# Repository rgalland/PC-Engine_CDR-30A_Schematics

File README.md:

This repository contains reverse engineering information regarding the PC-Engine CD-ROM2.

It started with the schematics of the main and front PCBs but has now evolve to provide reproduction parts. In the schematics, I attempted to highlight the differences between the CDR-30 (older models) and the CDR-30A but I have even found PCB differences within the newer CDR-30A units. Main difference is the use of the Sony DSP CXD1135 + external RAM as opposed to CXD1167 without additional RAM.
Currently available reproduction parts are the 2 flexible PCBs on the KSS-220A laser module. These are not compatible with the KSS-162A found mainly on older units. The main PCB is at the prototype level at the moment.

You will need kicad to work with files but I also provide pdf files to view the schematics in a more convenent way.

Current versions:
Original PCBs:
	- MAIN_PWR schematics: Rev0.3
	- FRONT_PWB schematics: Rev0.1
	
Reproduction PCBs:
	- KSS-220A Focus Tracking Flex PCB schematics and layout: Rev0.1
	- KSS-220A Lens Flex PCB schematics and layout: Rev0.1
	- Main PCB schematics and layout: Rev0.1

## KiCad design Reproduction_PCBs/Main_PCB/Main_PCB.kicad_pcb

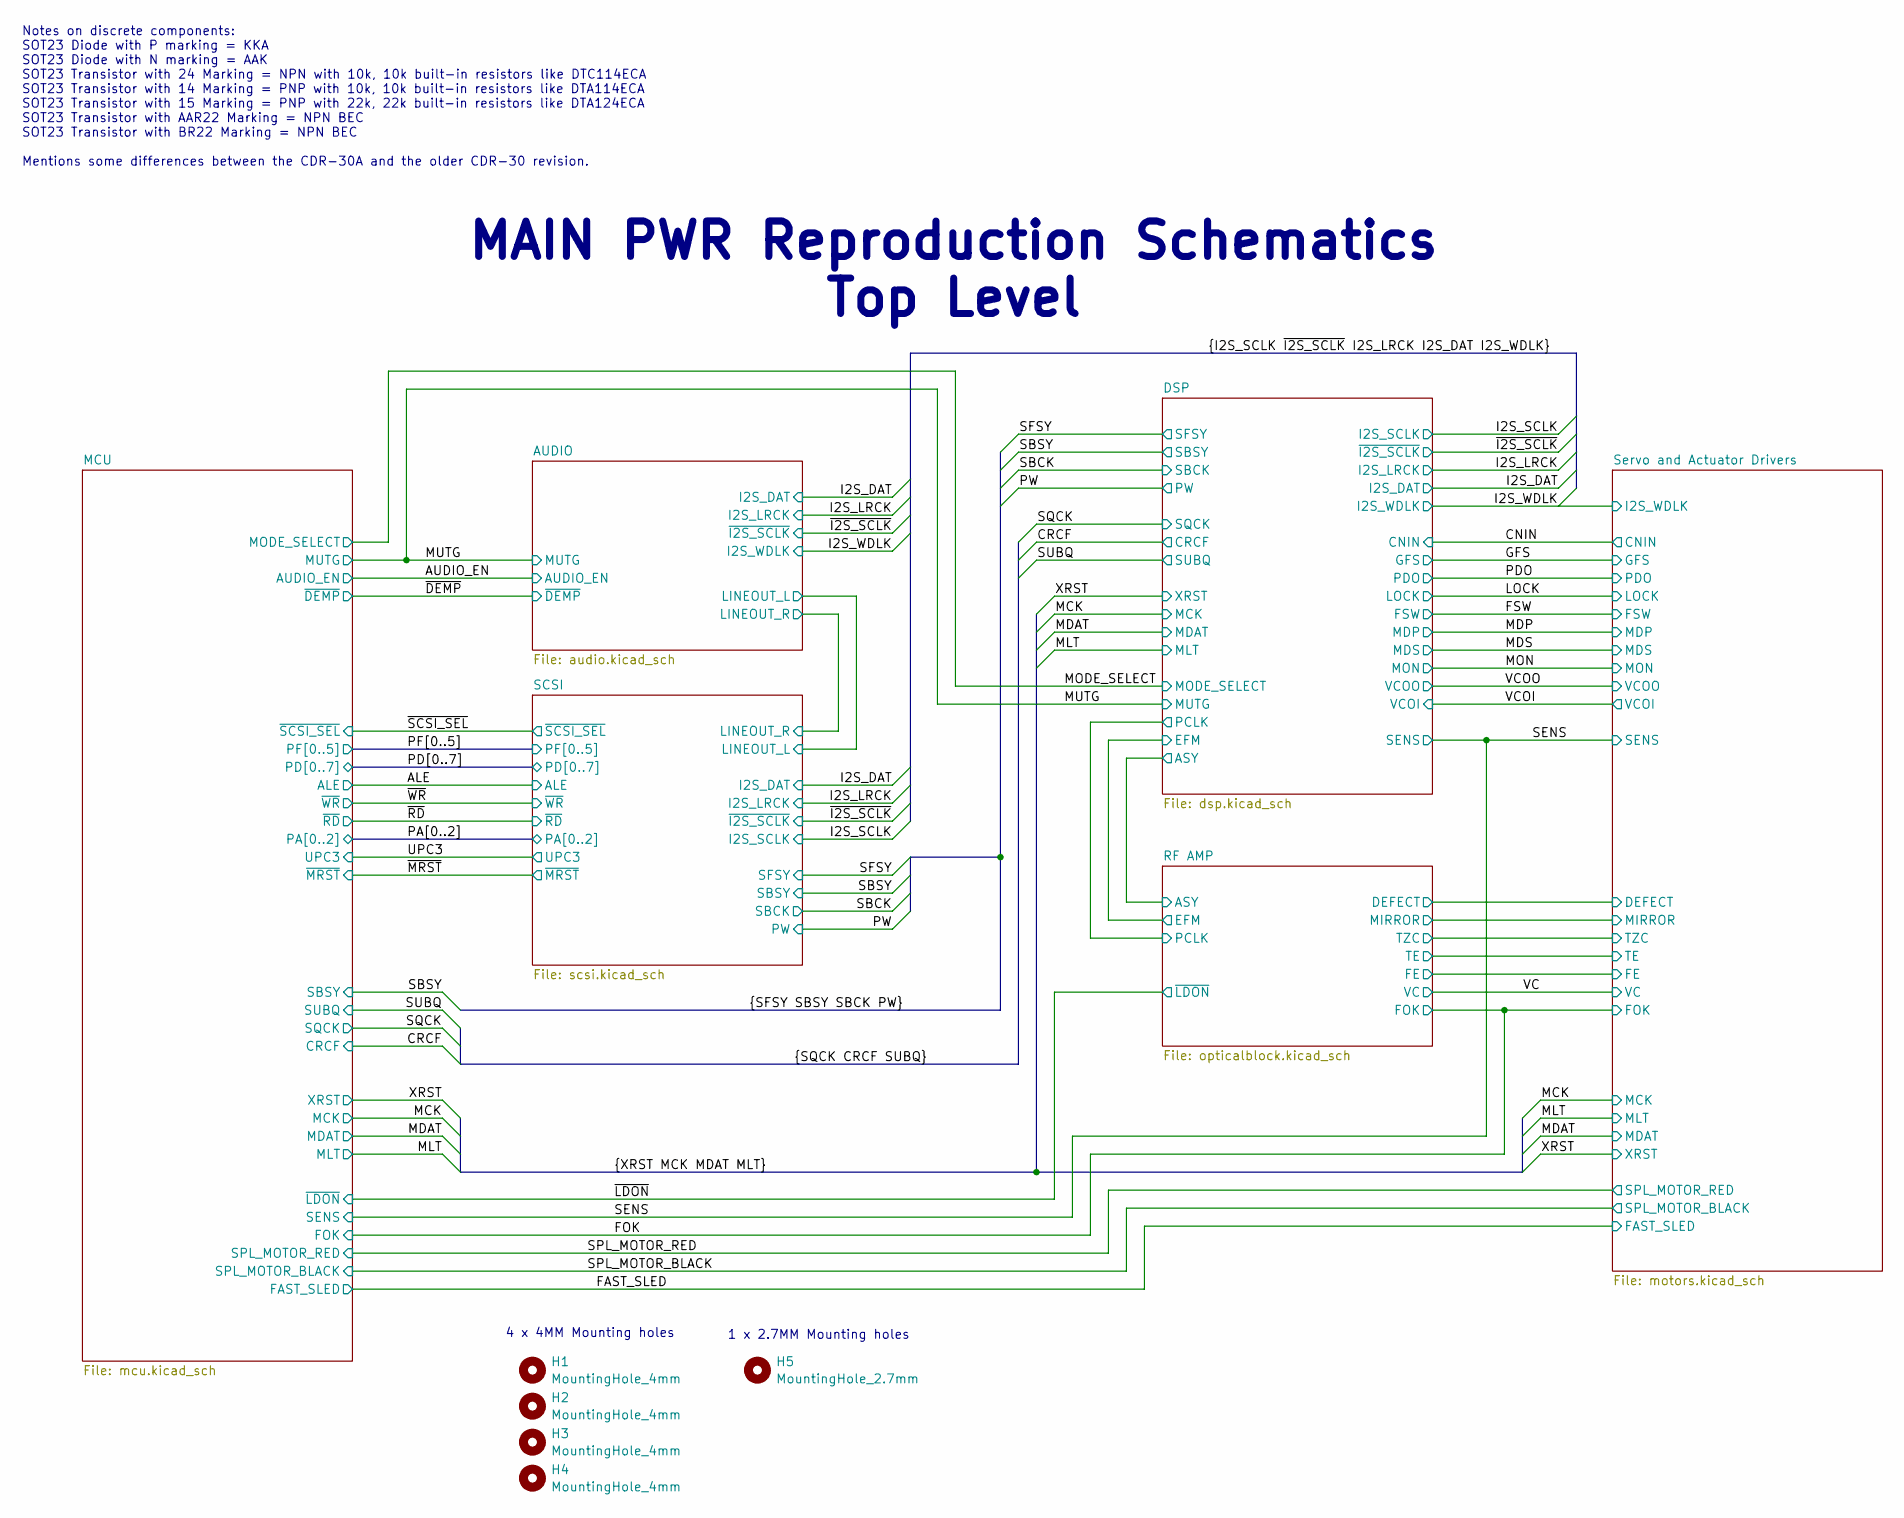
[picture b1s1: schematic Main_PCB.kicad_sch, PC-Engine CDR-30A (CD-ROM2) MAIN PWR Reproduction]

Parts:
H1, H2, H3, H4: MountingHole_4mm
H5: MountingHole_2.7mm

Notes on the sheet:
Notes on discrete components: SOT23 Diode with P marking = KKA SOT23 Diode with N marking = AAK SOT23 Transistor with 24 Marking = NPN with 10k, 10k built-in resistors like DTC114ECA SOT23 Transistor with 14 Marking = PNP with 10k, 10k built-in resistors like DTA114ECA SOT23 Transistor with 15 Mark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
4 x 4MM Mounting holes
1 x 2.7MM Mounting holes
MAIN PWR Reproduction Schematics Top Level

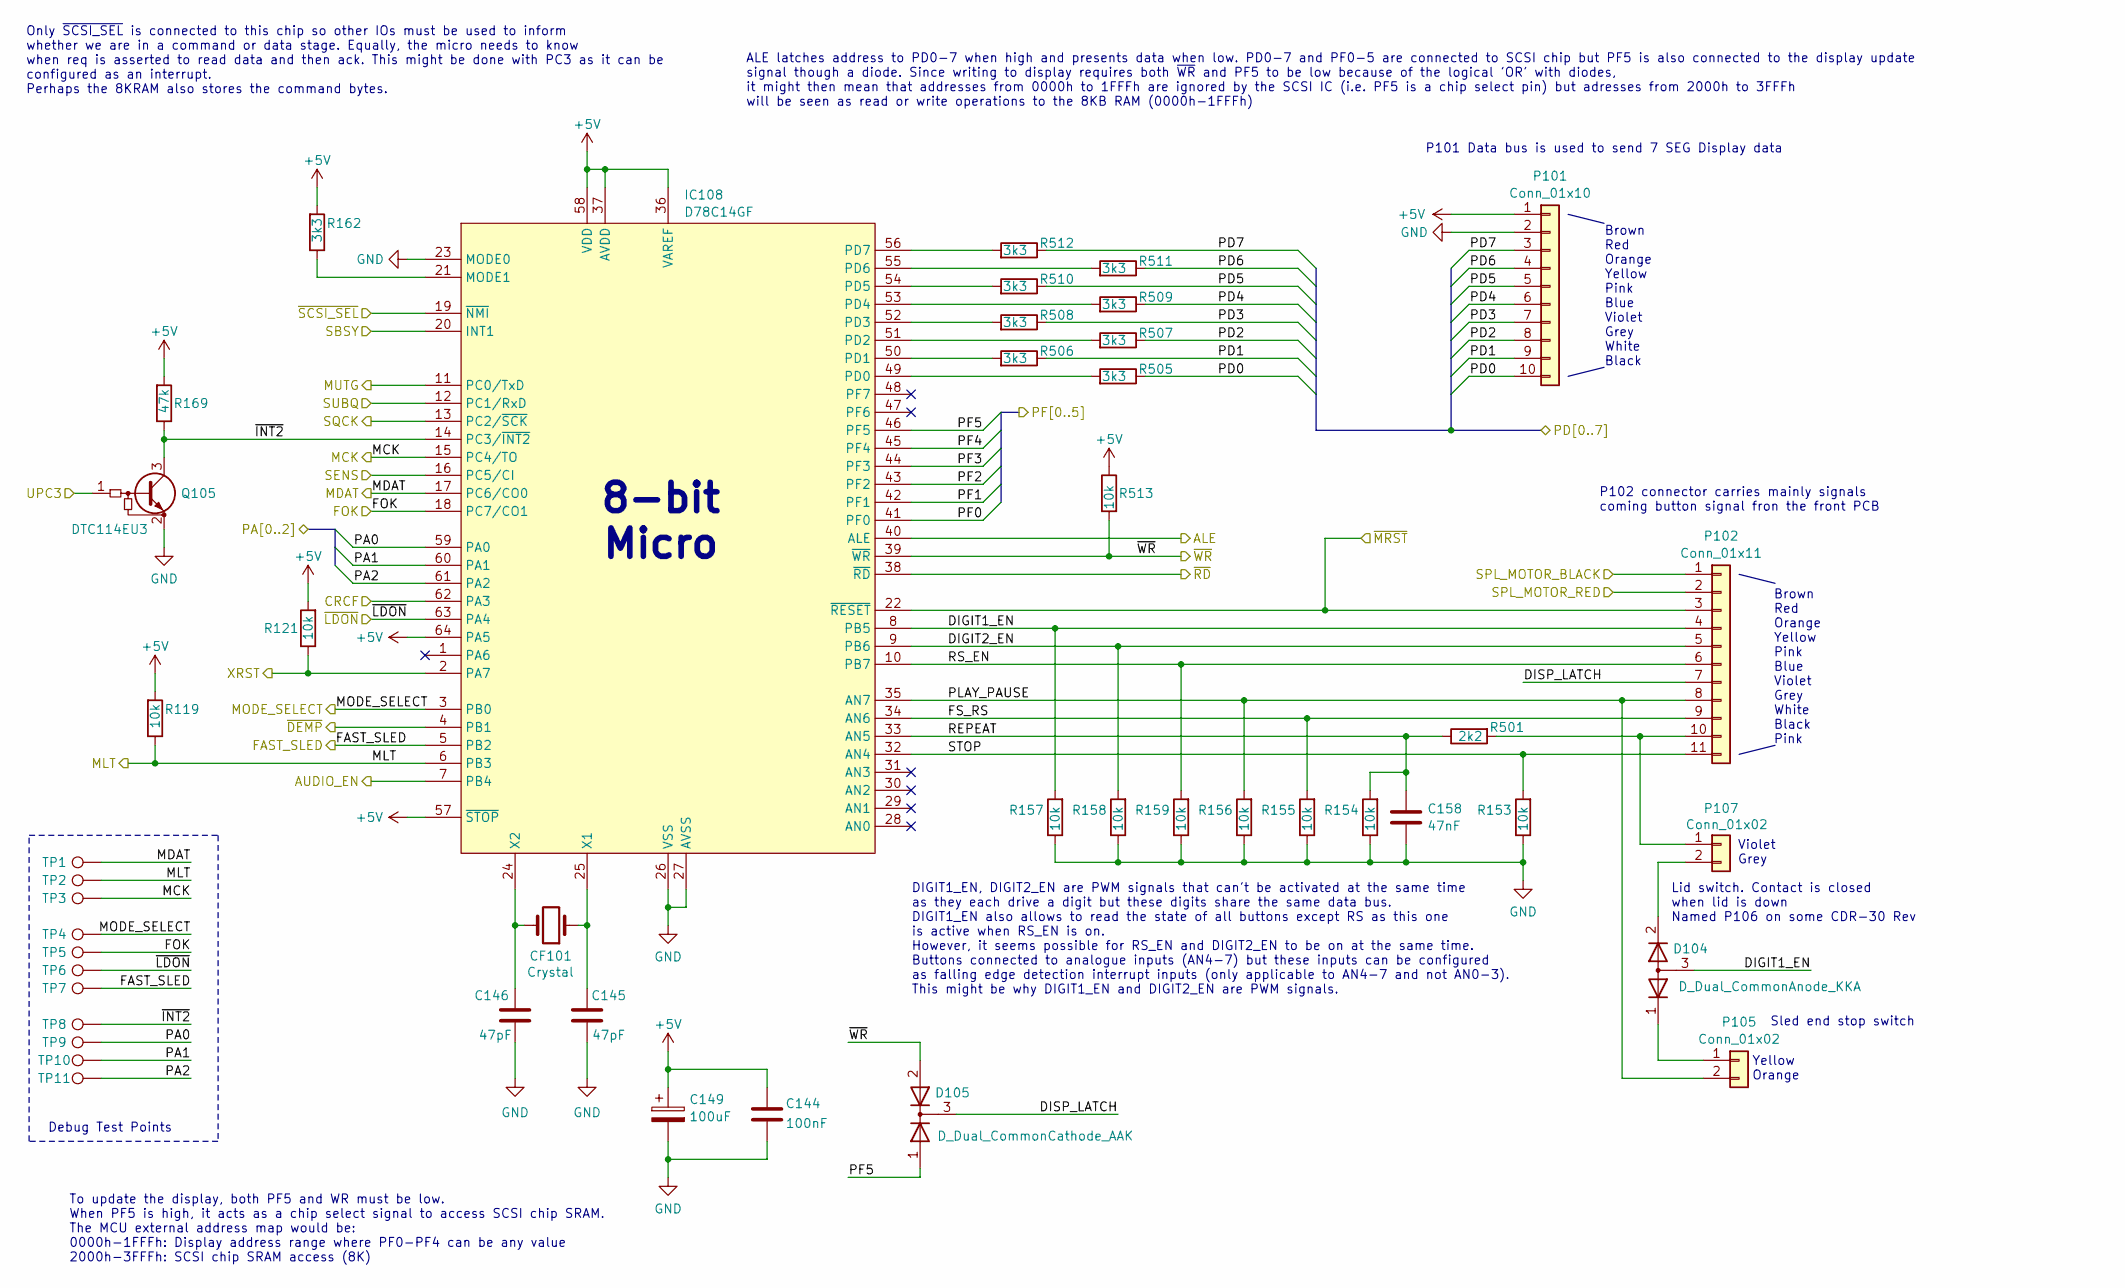
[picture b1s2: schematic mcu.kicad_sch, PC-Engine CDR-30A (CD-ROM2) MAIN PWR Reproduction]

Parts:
C144: 100nF; C_0603_1608Metric
C145, C146: 47pF; C_0603_1608Metric
C149: 100uF; CP_Elec_5x5.4
C158: 47nF; C_0603_1608Metric
CF101: Crystal; Crystal_HC18-U_Vertical
D104: D_Dual_CommonAnode_KKA; SOT-23
D105: D_Dual_CommonCathode_AAK; SOT-23
IC108: D78C14GF; PQFP-64_20x14mm_P1.0mm
P101: Conn_01x10; JST_ZH_B10B-ZR_1x10_P1.50mm_Vertical
P102: Conn_01x11; JST_ZH_B11B-ZR_1x11_P1.50mm_Vertical
P105, P107: Conn_01x02; JST_ZH_B2B-ZR_1x02_P1.50mm_Vertical
Q105: DTC114EU3; SOT-23
R119, R121, R153, R154, R155, R156, R157, R158, R159, R513: 10k; R_0603_1608Metric
R162, R505, R506, R507, R508, R509, R510, R511, R512: 3k3; R_0603_1608Metric
R169: 47k; R_0603_1608Metric
R501: 2k2; R_0603_1608Metric
TP1, TP2, TP3, TP4, TP5, TP6, TP7, TP8, TP9, TP10, TP11: TestPoint; TestPoint_Pad_D1.5mm

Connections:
+5V: C144.2, C149.1, IC108.36 (VAREF), IC108.37 (AVDD), IC108.57 (~STOP), IC108.58 (VDD), IC108.64 (PA5), P101.1, R119.2, R121.2, R162.2, R169.2, R513.1; also elsewhere on the board
/ALE: IC108.40 (ALE); also elsewhere on the board
/AUDIO_EN: IC108.7 (PB4); also elsewhere on the board
/CRCF: IC108.62 (PA3); also elsewhere on the board
/FAST_SLED: IC108.5 (PB2), TP7.1; also elsewhere on the board
/FOK: IC108.18 (PC7/CO1), TP5.1; also elsewhere on the board
/MCK: IC108.15 (PC4/TO), TP3.1; also elsewhere on the board
/MCU/DIGIT1_EN: D104.3 (A), IC108.8 (PB5), P102.4, R157.2
/MCU/DIGIT2_EN: IC108.9 (PB6), P102.5, R158.2
/MCU/DISP_LATCH: D105.3 (K), P102.7
/MCU/FS_RS: IC108.34 (AN6), P102.9, R155.2
/MCU/PLAY_PAUSE: IC108.35 (AN7), P102.8, P105.2, R156.2
/MCU/REPEAT: C158.1, IC108.33 (AN5), R154.2, R501.1
/MCU/RS_EN: IC108.10 (PB7), P102.6, R159.2
/MCU/STOP: IC108.32 (AN4), P102.11, R153.2
/MCU/~INT2: IC108.14 (PC3/~INT2), Q105.3 (C), R169.1, TP8.1
/MDAT: IC108.17 (PC6/CO0), TP1.1; also elsewhere on the board
/MLT: IC108.6 (PB3), R119.1, TP2.1; also elsewhere on the board
/MODE_SELECT: IC108.3 (PB0), TP4.1; also elsewhere on the board
/MUTG: IC108.11 (PC0/TxD); also elsewhere on the board
/PA0: IC108.59 (PA0), TP9.1; also elsewhere on the board
/PA1: IC108.60 (PA1), TP10.1; also elsewhere on the board
/PA2: IC108.61 (PA2), TP11.1; also elsewhere on the board
/PD0: P101.10, R505.1; also elsewhere on the board
/PD1: P101.9, R506.1; also elsewhere on the board
/PD2: P101.8, R507.1; also elsewhere on the board
/PD3: P101.7, R508.1; also elsewhere on the board
/PD4: P101.6, R509.1; also elsewhere on the board
/PD5: P101.5, R510.1; also elsewhere on the board
/PD6: P101.4, R511.1; also elsewhere on the board
/PD7: P101.3, R512.1; also elsewhere on the board
/PF0: IC108.41 (PF0); also elsewhere on the board
/PF1: IC108.42 (PF1); also elsewhere on the board
/PF2: IC108.43 (PF2); also elsewhere on the board
/PF3: IC108.44 (PF3); also elsewhere on the board
/PF4: IC108.45 (PF4); also elsewhere on the board
/PF5: D105.1 (A), IC108.46 (PF5); also elsewhere on the board
/SBSY: IC108.20 (INT1); also elsewhere on the board
/SENS: IC108.16 (PC5/CI); also elsewhere on the board
/SPL_MOTOR_BLACK: P102.1; also elsewhere on the board
/SPL_MOTOR_RED: P102.2; also elsewhere on the board
/SQCK: IC108.13 (PC2/~SCK); also elsewhere on the board
/SUBQ: IC108.12 (PC1/RxD); also elsewhere on the board
/UPC3: Q105.1 (B); also elsewhere on the board
/XRST: IC108.2 (PA7), R121.1; also elsewhere on the board
/~DEMP: IC108.4 (PB1); also elsewhere on the board
/~LDON: IC108.63 (PA4), TP6.1; also elsewhere on the board
/~MRST: IC108.22 (~RESET), P102.3; also elsewhere on the board
/~RD: IC108.38 (~RD); also elsewhere on the board
/~SCSI_SEL: IC108.19 (~NMI); also elsewhere on the board
/~WR: D105.2 (A), IC108.39 (~WR), R513.2; also elsewhere on the board
GND: C144.1, C145.2, C146.1, C149.2, C158.2, IC108.23 (MODE0), IC108.26 (VSS), IC108.27 (AVSS), P101.2, Q105.2 (E), R153.1, R154.1, R155.1, R156.1, R157.1, R158.1, R159.1; also elsewhere on the board
unnamed: IC108.21 (MODE1), R162.1
unnamed: IC108.49 (PD0), R505.2
unnamed: IC108.50 (PD1), R506.2
unnamed: IC108.51 (PD2), R507.2
unnamed: IC108.52 (PD3), R508.2
unnamed: IC108.53 (PD4), R509.2
unnamed: IC108.54 (PD5), R510.2
unnamed: IC108.55 (PD6), R511.2
unnamed: IC108.56 (PD7), R512.2
unnamed: C145.1, CF101.1, IC108.25 (X1)
unnamed: C146.2, CF101.2, IC108.24 (X2)
unnamed: P102.10, P107.1, R501.2
unnamed: D104.1 (K), P105.1
unnamed: D104.2 (K), P107.2

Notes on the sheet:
Lid switch. Contact is closed when lid is down Named P106 on some CDR-30 Rev
Brown Red Orange Yellow Pink Blue Violet Grey White Black
8-bit Micro
P102 connector carries mainly signals coming button signal fron the front PCB
ALE latches address to PD0-7 when high and presents data when low. PD0-7 and PF0-5 are connected to SCSI chip but PF5 is also connected to the display update signal though a diode. Since writing to display requires both ~{WR} and PF5 to be low because of the logical 'OR' with diodes, it might then 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
DIGIT1_EN, DIGIT2_EN are PWM signals that can't be activated at the same time as they each drive a digit but these digits share the same data bus. DIGIT1_EN also allows to read the state of all buttons except RS as this one is active when RS_EN is on. However, it seems possible for RS_EN and DIGIT2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
Brown Red Orange Yellow Pink Blue Violet Grey White Black Pink
To update the display, both PF5 and WR must be low. When PF5 is high, it acts as a chip select signal to access SCSI chip SRAM. The MCU external address map would be: 0000h-1FFFh: Display address range where PF0-PF4 can be any value 2000h-3FFFh: SCSI chip SRAM access (8K)
P101 Data bus is used to send 7 SEG Display data
Violet Grey
Debug Test Points
Sled end stop switch
Only ~{SCSI_SEL} is connected to this chip so other IOs must be used to inform whether we are in a command or data stage. Equally, the micro needs to know when req is asserted to read data and then ack. This might be done with PC3 as it can be configured as an interrupt. Perhaps the 8KRAM also stor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
Yellow Orange

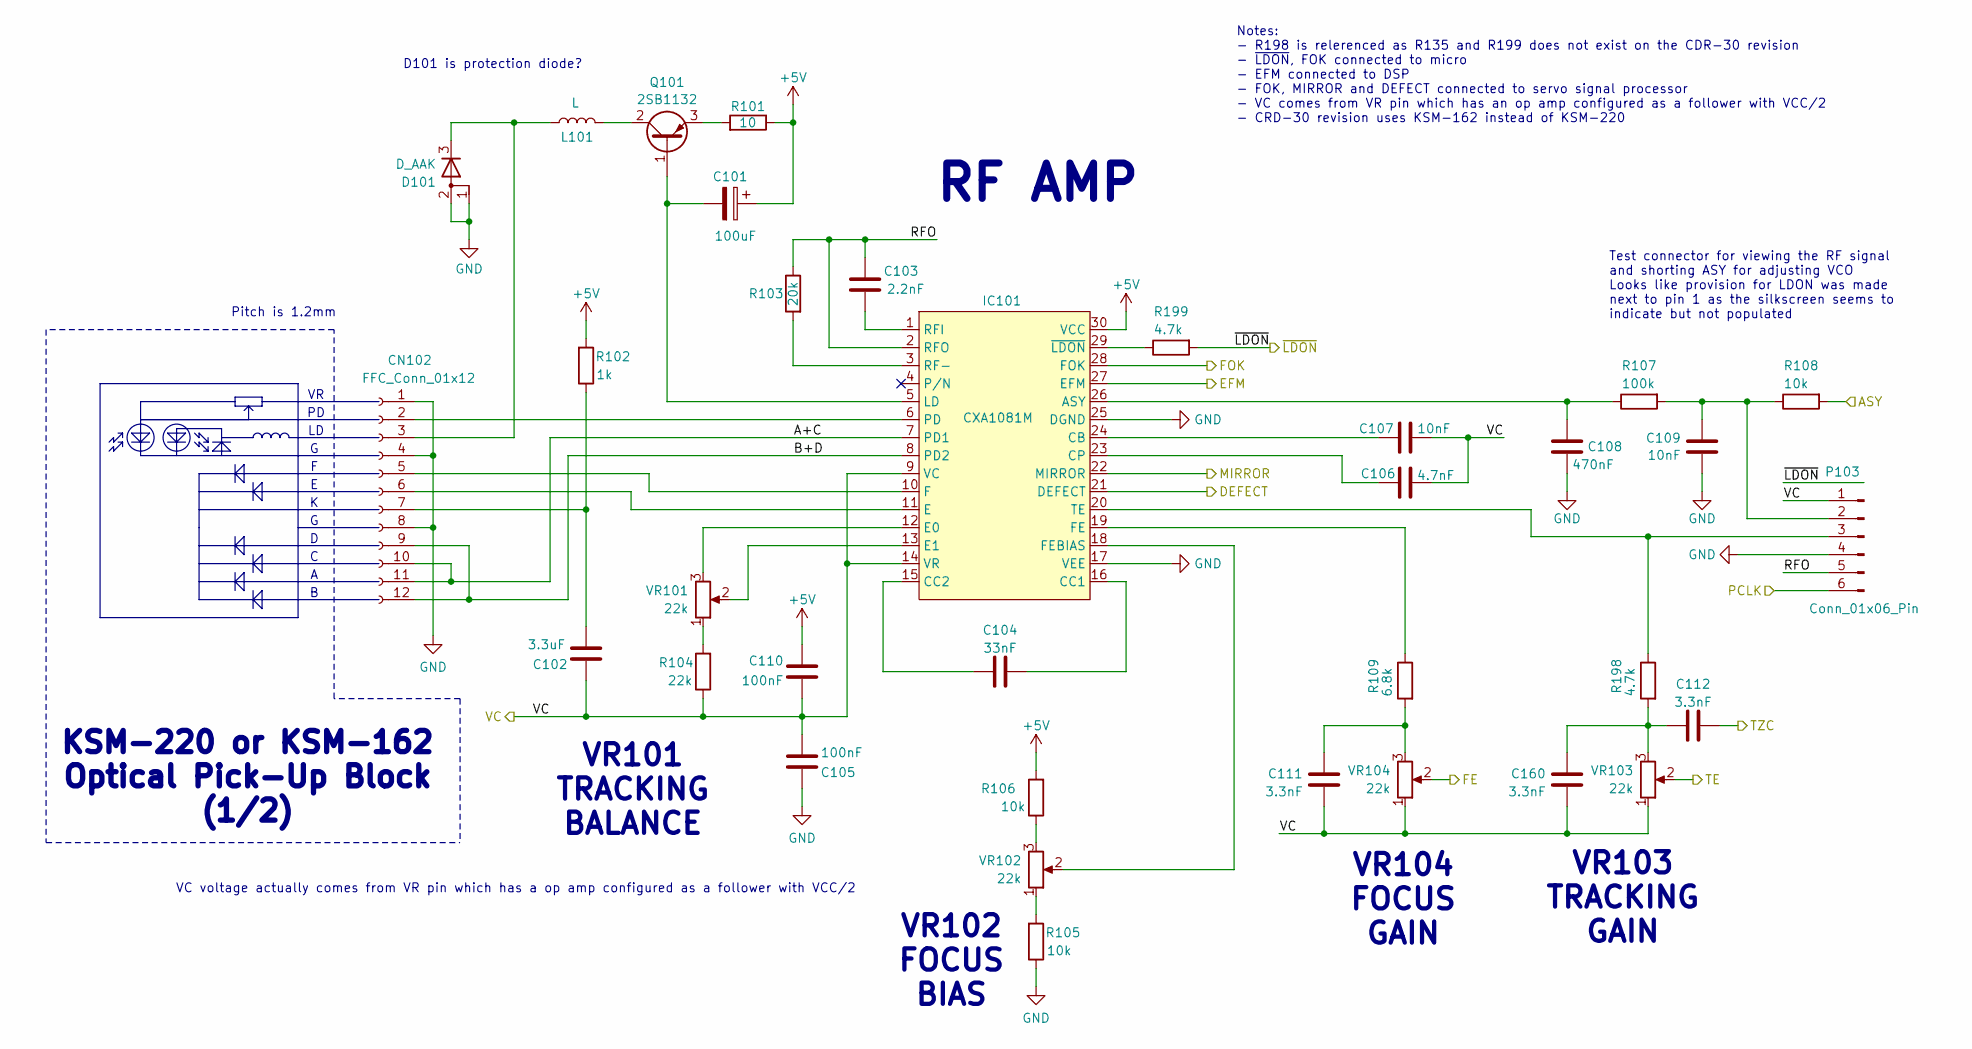
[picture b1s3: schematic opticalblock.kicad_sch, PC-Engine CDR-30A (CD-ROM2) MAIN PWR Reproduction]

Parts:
C101: 100uF; CP_Elec_5x5.4
C102: 3.3uF; C_0805_2012Metric
C103: 2.2nF; C_0603_1608Metric
C104: 33nF; C_0603_1608Metric
C105, C110: 100nF; C_0603_1608Metric
C106: 4.7nF; C_0603_1608Metric
C107, C109: 10nF; C_0603_1608Metric
C108: 470nF; C_0603_1608Metric
C111, C112, C160: 3.3nF; C_0603_1608Metric
CN102: FFC_Conn_01x12; FFC_01x12_P1.25mm_Vertical
D101: D_AAK; SOT-23
IC101: CXA1081M; SOIC-30W_7.5x20.0mm_P1.27mm
L101: L; L_Axial_L5.0mm_D3.6mm_P10.00mm_Horizontal_Murata_BL01RN1A2A2
P103: Conn_01x06_Pin; PinHeader_1x06_P2.00mm_Horizontal
Q101: 2SB1132; SOT-89-3
R101: 10; R_Axial_DIN0207_L6.3mm_D2.5mm_P10.16mm_Horizontal
R102: 1k; R_0603_1608Metric
R103: 20k; R_0603_1608Metric
R104: 22k; R_0603_1608Metric
R105, R106, R108: 10k; R_0603_1608Metric
R107: 100k; R_0603_1608Metric
R109: 6.8k; R_0603_1608Metric
R198, R199: 4.7k; R_0603_1608Metric
VR101, VR102, VR103, VR104: 22k; Potentiometer_ACP_CA6-H2,5_Horizontal

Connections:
+5V: C101.1, C110.2, IC101.30 (VCC), R101.1, R102.2, R106.2; also elsewhere on the board
/DSP/ASY: R108.2; also elsewhere on the board
/DSP/EFM: IC101.27 (EFM); also elsewhere on the board
/DSP/PCLK: P103.6; also elsewhere on the board
/FOK: IC101.28 (FOK); also elsewhere on the board
/RF AMP/A+C: CN102.10, CN102.11, IC101.7 (PD1)
/RF AMP/B+D: CN102.9, CN102.12, IC101.8 (PD2)
/RF AMP/DEFECT: IC101.21 (DEFECT); also elsewhere on the board
/RF AMP/MIRROR: IC101.22 (MIRROR); also elsewhere on the board
/RF AMP/RFO: C103.1, IC101.2 (RFO), P103.5, R103.1
/Servo and Actuator Drivers/FE: VR104.2; also elsewhere on the board
/Servo and Actuator Drivers/TE: VR103.2; also elsewhere on the board
/Servo and Actuator Drivers/TZC: C112.1; also elsewhere on the board
/VC: C102.2, C105.1, C106.1, C107.1, C110.1, C111.1, C160.1, IC101.9 (VC), IC101.14 (VR), P103.1, R104.1, VR103.1, VR104.1; also elsewhere on the board
/~LDON: R199.2; also elsewhere on the board
GND: C105.2, C108.2, C109.1, CN102.1, CN102.4, CN102.8, D101.1 (A), D101.2 (A), IC101.17 (VEE), IC101.25 (DGND), P103.4, R105.1; also elsewhere on the board
unnamed: C111.2, R109.2, VR104.3
unnamed: C112.2, C160.2, R198.2, VR103.3
unnamed: CN102.2, IC101.6 (PD)
unnamed: CN102.3, D101.3 (K), L101.1
unnamed: CN102.5, IC101.10 (F)
unnamed: CN102.6, IC101.11 (E)
unnamed: C102.1, CN102.7, R102.1
unnamed: C108.1, IC101.26 (ASY), R107.1
unnamed: C107.2, IC101.24 (CB)
unnamed: C104.2, IC101.16 (CC1)
unnamed: C104.1, IC101.15 (CC2)
unnamed: C106.2, IC101.23 (CP)
unnamed: IC101.12 (E0), VR101.3
unnamed: IC101.13 (E1), VR101.2
unnamed: IC101.19 (FE), R109.1
unnamed: IC101.18 (FEBIAS), VR102.2
unnamed: C101.2, IC101.5 (LD), Q101.1 (B)
unnamed: IC101.3 (RF-), R103.2
unnamed: C103.2, IC101.1 (RFI)
unnamed: IC101.20 (TE), P103.3, R198.1
unnamed: IC101.29 (~LDON), R199.1
unnamed: C109.2, P103.2, R107.2, R108.1
unnamed: L101.2, Q101.2 (C)
unnamed: Q101.3 (E), R101.2
unnamed: R104.2, VR101.1
unnamed: R105.2, VR102.1
unnamed: R106.1, VR102.3

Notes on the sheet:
RF AMP
Pitch is 1.2mm
Test connector for viewing the RF signal and shorting ASY for adjusting VCO Looks like provision for LDON was made next to pin 1 as the silkscreen seems to indicate but not populated
Notes: - R198 is relerenced as R135 and R199 does not exist on the CDR-30 revision - ~{LDON}, FOK connected to micro - EFM connected to DSP - FOK, MIRROR and DEFECT connected to servo signal processor - VC comes from VR pin which has an op amp configured as a follower with VCC/2 - CRD-30 revision u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
D101 is protection diode?
KSM-220 or KSM-162 Optical Pick-Up Block (1/2)
VR103 TRACKING GAIN
VC voltage actually comes from VR pin which has a op amp configured as a follower with VCC/2
VR104 FOCUS GAIN
VR101 TRACKING BALANCE
VR102 FOCUS BIAS

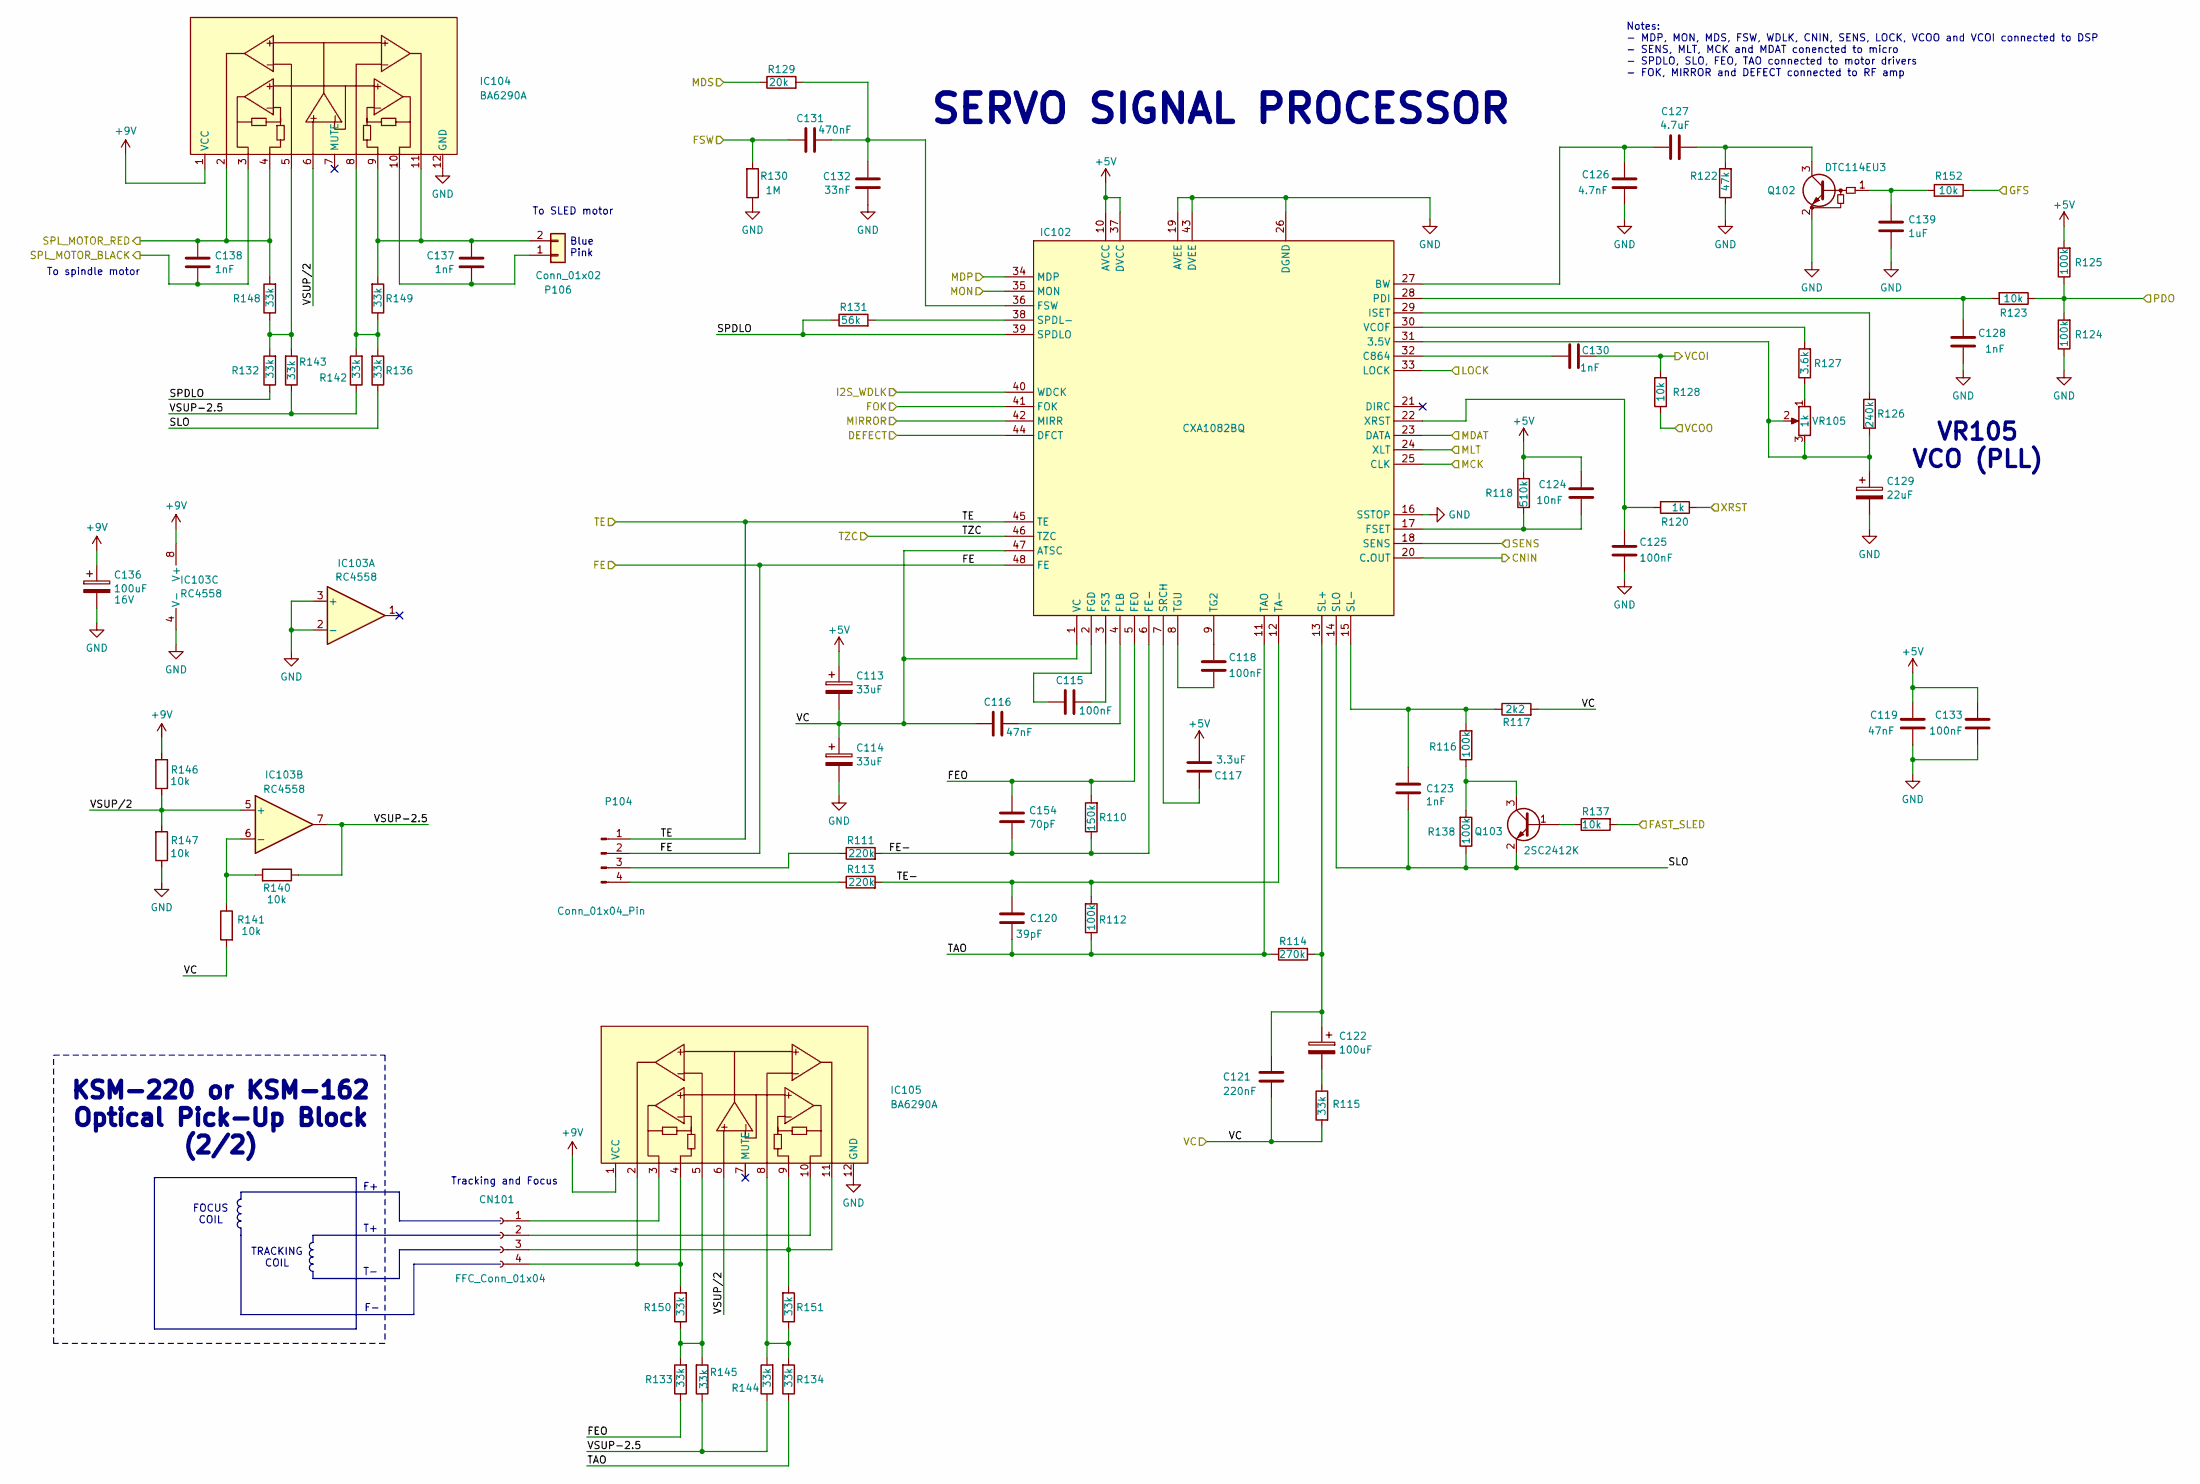
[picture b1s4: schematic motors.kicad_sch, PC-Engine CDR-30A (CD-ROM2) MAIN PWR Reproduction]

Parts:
C113, C114: 33uF; CP_Elec_5x5.4
C115, C118, C125, C133: 100nF; C_0603_1608Metric
C116, C119: 47nF; C_0603_1608Metric
C117: 3.3uF; C_0805_2012Metric
C120: 39pF; C_0603_1608Metric
C121: 220nF; C_0603_1608Metric
C122: 100uF; CP_Elec_5x5.4
C123, C128, C130, C137, C138: 1nF; C_0603_1608Metric
C124: 10nF; C_0603_1608Metric
C126: 4.7nF; C_0603_1608Metric
C127: 4.7uF; C_0805_2012Metric
C129: 22uF; CP_Elec_4x5.4
C131: 470nF; C_0603_1608Metric
C132: 33nF; C_0603_1608Metric
C136: 100uF; CP_Elec_6.3x5.4; Voltage 16V
C139: 1uF; C_0603_1608Metric
C154: 70pF; C_0603_1608Metric
CN101: FFC_Conn_01x04; FFC_01x04_P1.25mm_Vertical
IC102: CXA1082BQ; LQFP-48_12x12mm_P0.8mm
IC103: RC4558; SOIC-8_3.9x4.9mm_P1.27mm
IC104, IC105: BA6290A; TerminalBlock_TE_1-282834-2_1x12_P2.54mm_Horizontal
P104: Conn_01x04_Pin; PinHeader_1x04_P2.00mm_Horizontal
P106: Conn_01x02; JST_ZH_B2B-ZR_1x02_P1.50mm_Vertical
Q102: DTC114EU3; SOT-23
Q103: 2SC2412K; SOT-23
R110: 150k; R_0603_1608Metric
R111, R113: 220k; R_0603_1608Metric
R112, R116, R124, R125, R138: 100k; R_0603_1608Metric
R114: 270k; R_0603_1608Metric
R115, R132, R133, R134, R136, R142, R143, R144, R145, R148, R149, R150, R151: 33k; R_0603_1608Metric
R117: 2k2; R_0603_1608Metric
R118: 510k; R_0603_1608Metric
R120: 1k; R_0603_1608Metric
R122: 47k; R_0603_1608Metric
R123, R128, R137, R140, R141, R146, R147, R152: 10k; R_0603_1608Metric
R126: 240k; R_0603_1608Metric
R127: 3.6k; R_0603_1608Metric
R129: 20k; R_0603_1608Metric
R130: 1M; R_0603_1608Metric
R131: 56k; R_0603_1608Metric
VR105: 1k; Potentiometer_ACP_CA6-H2,5_Horizontal

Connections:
+5V: C113.1, C117.1, C119.2, C124.2, C133.2, IC102.10 (AVCC), IC102.37 (DVCC), R118.1, R125.2; also elsewhere on the board
+9V: C136.1, IC103.8 (V+), IC104.1 (VCC), IC105.1 (VCC), R146.2; also elsewhere on the board
/CNIN: IC102.20 (C.OUT); also elsewhere on the board
/FAST_SLED: R137.2; also elsewhere on the board
/FOK: IC102.41 (FOK); also elsewhere on the board
/FSW: C131.1, R130.2; also elsewhere on the board
/GFS: R152.1; also elsewhere on the board
/I2S_WDLK: IC102.40 (WDCK); also elsewhere on the board
/LOCK: IC102.33 (LOCK); also elsewhere on the board
/MCK: IC102.25 (CLK); also elsewhere on the board
/MDAT: IC102.23 (DATA); also elsewhere on the board
/MDP: IC102.34 (MDP); also elsewhere on the board
/MDS: R129.1; also elsewhere on the board
/MLT: IC102.24 (XLT); also elsewhere on the board
/MON: IC102.35 (MON); also elsewhere on the board
/PDO: R123.1, R124.2, R125.1; also elsewhere on the board
/RF AMP/DEFECT: IC102.44 (DFCT); also elsewhere on the board
/RF AMP/MIRROR: IC102.42 (MIRR); also elsewhere on the board
/SENS: IC102.18 (SENS); also elsewhere on the board
/SPL_MOTOR_BLACK: C138.2, IC104.3; also elsewhere on the board
/SPL_MOTOR_RED: C138.1, IC104.2, IC104.4, R148.2; also elsewhere on the board
/Servo and Actuator Drivers/FE: IC102.48 (FE), P104.2; also elsewhere on the board
/Servo and Actuator Drivers/FE-: C154.2, IC102.6 (FE-), R110.1, R111.2
/Servo and Actuator Drivers/FEO: C154.1, IC102.5 (FEO), R110.2, R133.1
/Servo and Actuator Drivers/SLO: C123.2, IC102.14 (SLO), Q103.2 (E), R136.1, R138.1
/Servo and Actuator Drivers/SPDLO: IC102.39 (SPDLO), R131.1, R132.1
/Servo and Actuator Drivers/TAO: C120.2, IC102.11 (TAO), R112.1, R114.2, R134.1
/Servo and Actuator Drivers/TE: IC102.45 (TE), P104.1; also elsewhere on the board
/Servo and Actuator Drivers/TE-: C120.1, IC102.12 (TA-), R112.2, R113.2
/Servo and Actuator Drivers/TZC: IC102.46 (TZC); also elsewhere on the board
/Servo and Actuator Drivers/VSUP-2.5: IC103.7, R140.1, R142.1, R143.1, R144.1, R145.1
/Servo and Actuator Drivers/VSUP/2: IC103.5 (+), IC104.6, IC105.6, R146.1, R147.2
/VC: C113.2, C114.1, C116.2, C121.2, IC102.1 (VC), IC102.47 (ATSC), R115.2, R117.2, R141.2; also elsewhere on the board
/VCOI: C130.1, R128.2; also elsewhere on the board
/VCOO: R128.1; also elsewhere on the board
/XRST: R120.1; also elsewhere on the board
GND: C114.2, C119.1, C125.1, C126.1, C128.1, C129.2, C132.1, C133.1, C136.2, C139.2, IC102.16 (SSTOP), IC102.19 (AVEE), IC102.26 (DGND), IC102.43 (DVEE), IC103.2 (-), IC103.3 (+), IC103.4 (V-), IC104.12 (GND), IC105.12 (GND), Q102.2 (E), R122.1, R124.1, R130.1, R147.1; also elsewhere on the board
unnamed: C122.2, R115.1
unnamed: CN101.1, IC105.3
unnamed: CN101.2, IC105.10
unnamed: CN101.3, IC105.9, IC105.11, R151.2
unnamed: CN101.4, IC105.2, IC105.4, R150.2
unnamed: C129.1, IC102.31 (3.5V), R126.2, VR105.2, VR105.3
unnamed: C126.2, C127.1, IC102.27 (BW)
unnamed: C130.2, IC102.32 (C864)
unnamed: C115.2, IC102.2 (FGD)
unnamed: C116.1, IC102.4 (FLB)
unnamed: C115.1, IC102.3 (FS3)
unnamed: C124.1, IC102.17 (FSET), R118.2
unnamed: C131.2, C132.2, IC102.36 (FSW), R129.2
unnamed: IC102.29 (ISET), R126.1
unnamed: C128.2, IC102.28 (PDI), R123.2
unnamed: C121.1, C122.1, IC102.13 (SL+), R114.1
unnamed: C123.1, IC102.15 (SL-), R116.2, R117.1
unnamed: IC102.38 (SPDL-), R131.2
unnamed: C117.2, IC102.7 (SRCH)
unnamed: C118.2, IC102.9 (TG2)
unnamed: C118.1, IC102.8 (TGU)
unnamed: IC102.30 (VCOF), R127.2
unnamed: C125.2, IC102.22 (XRST), R120.2
unnamed: IC103.6 (-), R140.2, R141.1
unnamed: IC104.5, R132.2, R143.2, R148.1
unnamed: IC104.8, R136.2, R142.2, R149.1
unnamed: IC105.5, R133.2, R145.2, R150.1
unnamed: IC105.8, R134.2, R144.2, R151.1
unnamed: P104.3, R111.1
unnamed: P104.4, R113.1
unnamed: C137.2, IC104.10, P106.1
unnamed: C137.1, IC104.9, IC104.11, P106.2, R149.2
unnamed: C139.1, Q102.1 (B), R152.2
unnamed: C127.2, Q102.3 (C), R122.2
unnamed: Q103.1 (B), R137.1
unnamed: Q103.3 (C), R116.1, R138.2
unnamed: R127.1, VR105.1

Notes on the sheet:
To SLED motor
Notes: - MDP, MON, MDS, FSW, WDLK, CNIN, SENS, LOCK, VCOO and VCOI connected to DSP - SENS, MLT, MCK and MDAT conencted to micro - SPDLO, SLO, FEO, TAO connected to motor drivers - FOK, MIRROR and DEFECT connected to RF amp
SERVO SIGNAL PROCESSOR
Blue Pink
KSM-220 or KSM-162 Optical Pick-Up Block (2/2)
TRACKING COIL
FOCUS COIL
To spindle motor
Tracking and Focus
VR105 VCO (PLL)
